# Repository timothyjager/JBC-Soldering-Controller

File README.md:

# JBC-Soldering-Controller

The idea of this project is to make a simple JBC soldering station for the T245. It runs from a 24V DC power supply.
Please note: I burnt out a C210 cartridge using this. I think it would be ok if there was power limiting, so I will try that at some point. 

Tested:

T245 soldering iron

Not tested:

Software - I have kept this because it might be fun to play with at some point, but it is not tested.

AM120 Micro Tweezers (I have not got any yet :( )

Todo:

Automatically changing the GUI depending on if you are using the standard iron or the tweezers.

Possibly change PCB design to make it fit in a box nicely

Design a case for it

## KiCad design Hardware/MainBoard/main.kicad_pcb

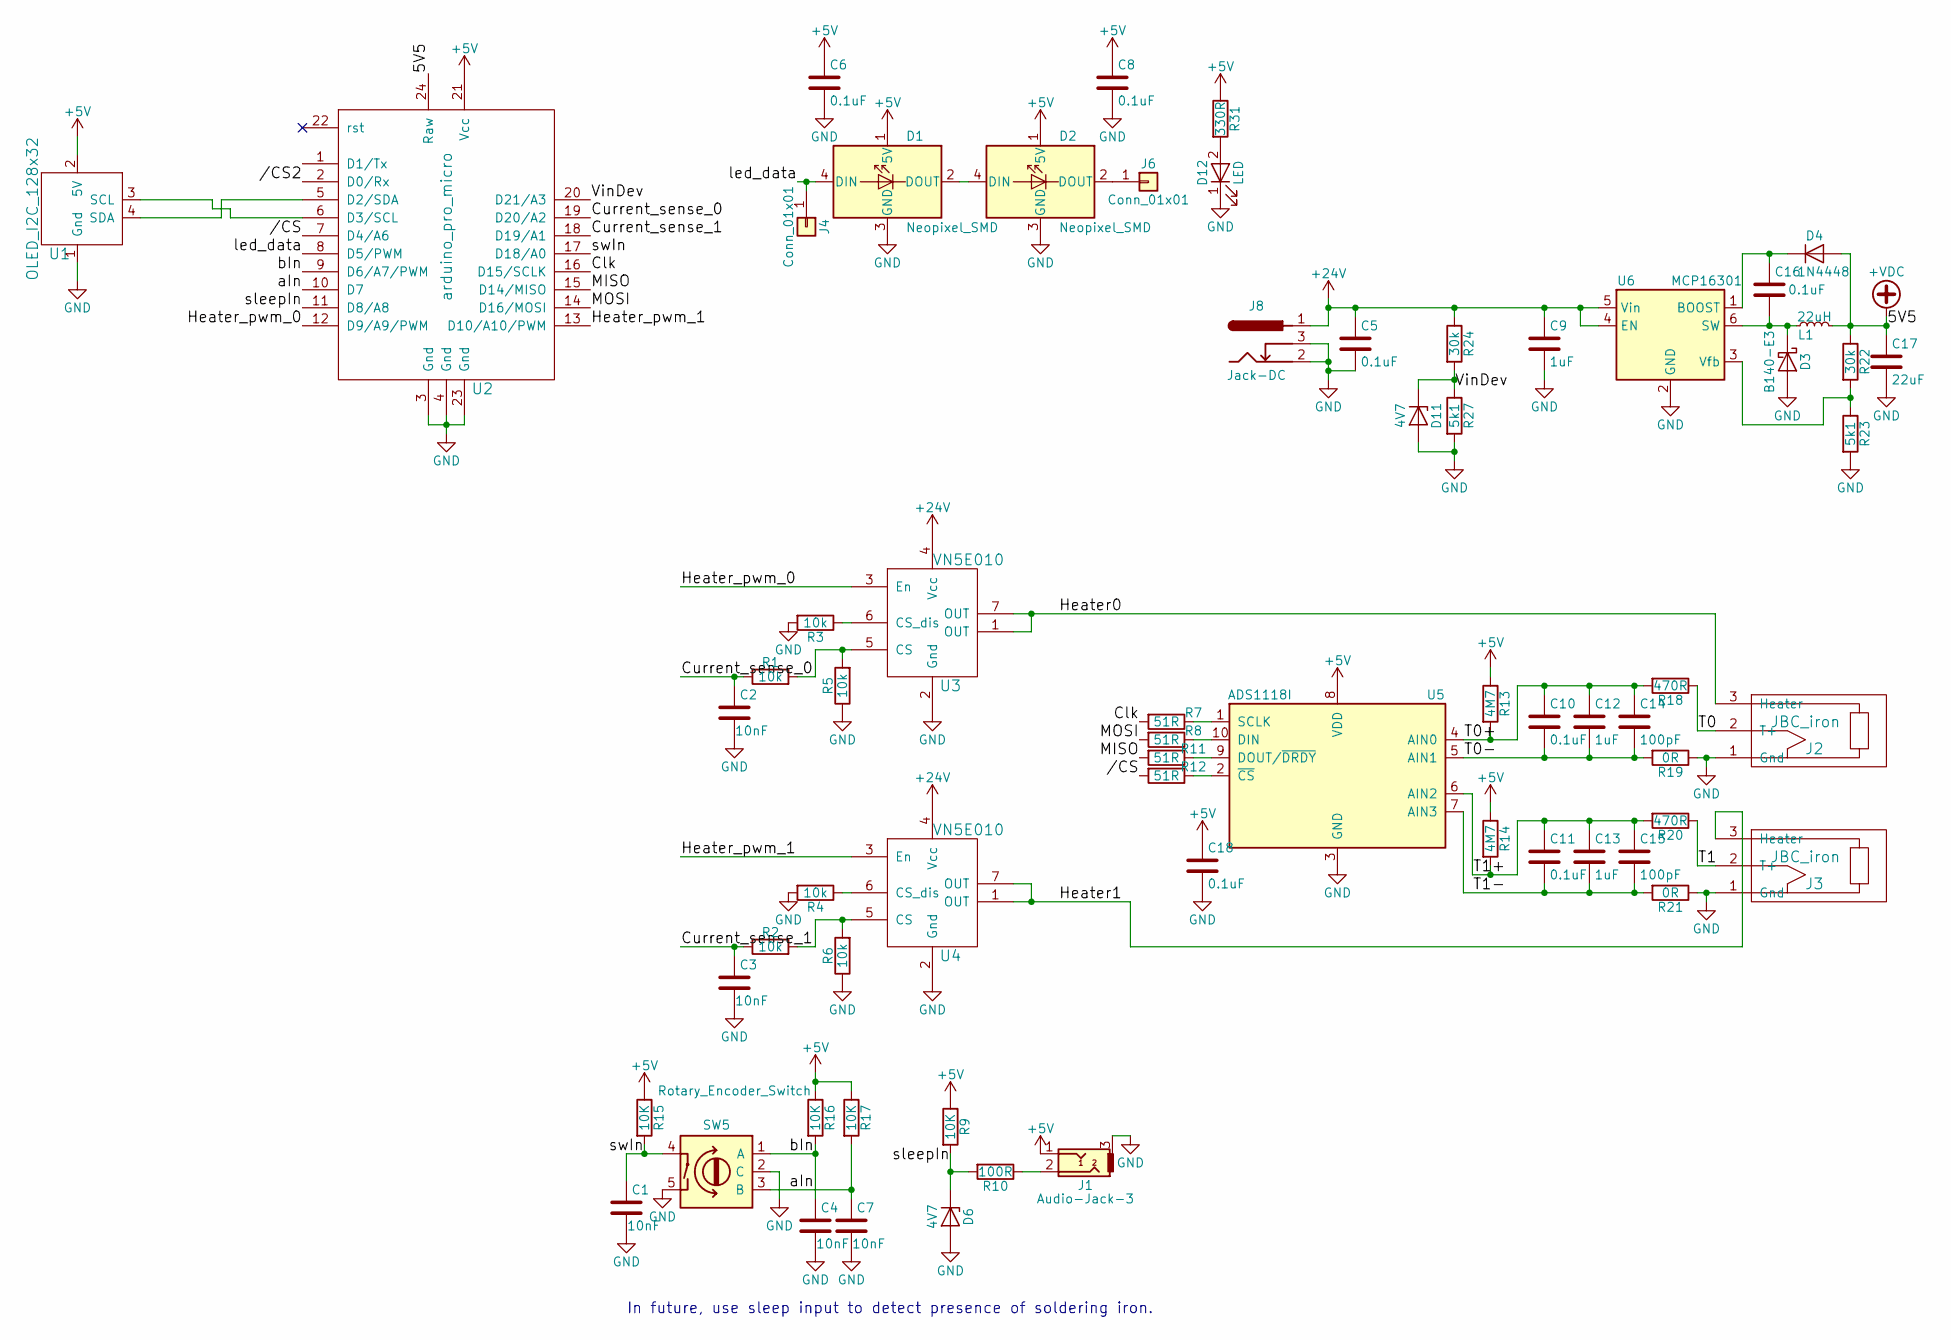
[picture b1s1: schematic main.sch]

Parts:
C1, C2, C3, C4, C7: 10nF; C_0805_HandSoldering
C5, C6, C8, C10, C11, C16, C18: 0.1uF; C_0805_HandSoldering
C9, C12, C13: 1uF; C_0805_HandSoldering
C14, C15: 100pF; C_0805_HandSoldering
C17: 22uF; C_0805_HandSoldering
D1, D2: Neopixel_SMD; 5050-4(L)
D3: B140-E3; D_SMA
D4: 1N4448; D_SOD-123F
D6, D11: 4V7; D_SOD-123F; MPN BZT52-C4V7X
D12: LED; LED_0805_HandSoldering
J1: Audio-Jack-3; 3.5mm_jack; MPN MJ4435-R
J2, J3: JBC_iron; PhoenixContact_MSTBVA-G_03x5.08mm_Vertical
J4, J6: Conn_01x01; Pin_Header_Straight_1x01_Pitch2.54mm
J8: Jack-DC; JACK_ALIM
L1: 22uH; L_6.3x6.3_H3; MPN SRN6045-220M
R1, R2, R3, R4, R5, R6: 10k; R_0805_HandSoldering
R7, R8, R11, R12: 51R; R_0805_HandSoldering
R9, R15, R16, R17: 10K; R_0805_HandSoldering
R10: 100R; R_0805_HandSoldering
R13, R14: 4M7; R_0805_HandSoldering
R18, R20: 470R; R_0805_HandSoldering
R19, R21: 0R; R_0805_HandSoldering
R22, R24: 30k; R_0805_HandSoldering
R23, R27: 5k1; R_0805_HandSoldering
R31: 330R; R_0805_HandSoldering
SW5: Rotary_Encoder_Switch; rot_encoder
U1: OLED_I2C_128x32
U2: arduino_pro_micro; DIP-24_W15.24mm_LongPads
U3, U4: VN5E010; HPAK; MPN VN5E010AHTR-E
U5: ADS1118I; VSSOP_10_HandSoldered; MPN ADS1118IDGST
U6: MCP16301; SOT-23-6; MPN MCP16301T-E/CH

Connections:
+5V: C6.1, C8.1, C18.1, D1.1 (5V), D2.1 (5V), J1.1, R9.1, R13.1, R14.1, R15.1, R16.1, R17.1, R31.1, U1.2 (5V), U2.21 (Vcc), U5.8 (VDD)
+24V: C5.1, C9.1, J8.1, R24.1, U3.4 (Vcc), U4.4 (Vcc), U6.4 (EN), U6.5 (Vin)
+VDC: C17.1, D4.2 (A), L1.2, R22.1, U2.24 (Raw)
//CS: R12.2, U2.7 (D4/A6)
//CS2: U2.2 (D0/Rx)
/Clk: R7.2, U2.16 (D15/SCLK)
/Current_sense_0: C2.1, R1.1, U2.19 (D20/A2)
/Current_sense_1: C3.1, R2.1, U2.18 (D19/A1)
/Heater0: J2.3 (Heater), U3.1 (OUT), U3.7 (OUT)
/Heater1: J3.3 (Heater), U4.1 (OUT), U4.7 (OUT)
/Heater_pwm_0: U2.12 (D9/A9/PWM), U3.3 (En)
/Heater_pwm_1: U2.13 (D10/A10/PWM), U4.3 (En)
/MISO: R11.2, U2.15 (D14/MISO)
/MOSI: R8.2, U2.14 (D16/MOSI)
/T0: J2.2 (T+), R18.1
/T0+: C10.1, C12.1, C14.1, R13.2, R18.2, U5.4 (AIN0)
/T0-: C10.2, C12.2, C14.2, R19.2, U5.5 (AIN1)
/T1: J3.2 (T+), R20.1
/T1+: C11.1, C13.1, C15.1, R14.2, R20.2, U5.6 (AIN2)
/T1-: C11.2, C13.2, C15.2, R21.2, U5.7 (AIN3)
/VinDev: D11.1 (K), R24.2, R27.1, U2.20 (D21/A3)
/aIn: C7.1, R17.2, SW5.3 (B), U2.10 (D7)
/bIn: C4.1, R16.2, SW5.1 (A), U2.9 (D6/A7/PWM)
/led_data: D1.4 (DIN), J4.1, U2.8 (D5/PWM)
/sleepIn: D6.1 (K), R9.2, R10.2, U2.11 (D8/A8)
/swIn: C1.1, R15.2, SW5.4, U2.17 (D18/A0)
GND: C1.2, C2.2, C3.2, C4.2, C5.2, C6.2, C7.2, C8.2, C9.2, C17.2, C18.2, D1.3 (GND), D2.3 (GND), D3.2 (A), D6.2 (A), D11.2 (A), D12.1 (K), J1.3, J2.1 (Gnd), J3.1 (Gnd), J8.2, J8.3, R3.2, R4.2, R5.1, R6.1, R19.1, R21.1, R23.2, R27.2, SW5.2 (C), SW5.5, U1.1 (Gnd), U2.3 (Gnd), U2.4 (Gnd), U2.23 (Gnd), U3.2 (Gnd), U4.2 (Gnd), U5.3 (GND), U6.2 (GND)
unnamed: C16.1, D4.1 (K), U6.1 (BOOST)
unnamed: C16.2, D3.1 (K), L1.1, U6.6 (SW)
unnamed: D1.2 (DOUT), D2.4 (DIN)
unnamed: D2.2 (DOUT), J6.1
unnamed: D12.2 (A), R31.2
unnamed: J1.2, R10.1
unnamed: R1.2, R5.2, U3.5 (CS)
unnamed: R2.2, R6.2, U4.5 (CS)
unnamed: R3.1, U3.6 (CS_dis)
unnamed: R4.1, U4.6 (CS_dis)
unnamed: R7.1, U5.1 (SCLK)
unnamed: R8.1, U5.10 (DIN)
unnamed: R11.1, U5.9 (DOUT/~DRDY)
unnamed: R12.1, U5.2 (~CS)
unnamed: R22.2, R23.1, U6.3 (Vfb)
unnamed: U1.3 (SCL), U2.6 (D3/SCL)
unnamed: U1.4 (SDA), U2.5 (D2/SDA)

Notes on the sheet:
In future, use sleep input to detect presence of soldering iron.

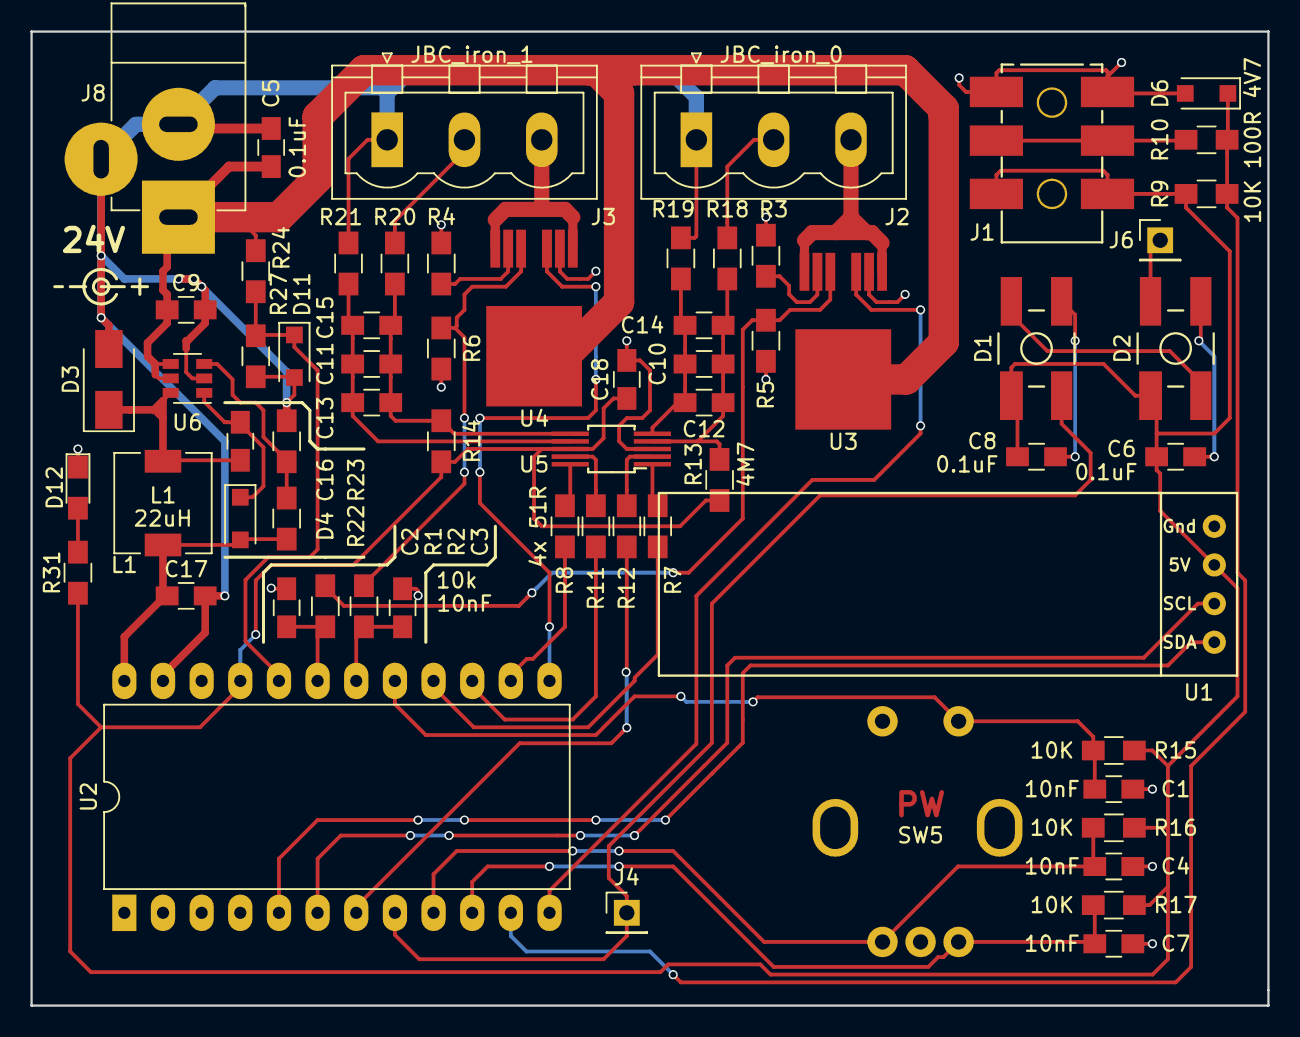
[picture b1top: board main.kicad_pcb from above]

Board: 2 copper layers, 81.3 x 64.0 mm, 65 parts (0 on the bottom side), 43 nets.

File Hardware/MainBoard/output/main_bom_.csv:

Component,Description,Part,References,Value,Footprint,Quantity Per PCB,Datasheet,SPURL,Cost ea @ 100qty,MPN,MFR,SPN,SPR
1,Unpolarized capacitor,C,C5 C6 C8 C10 C11 C16 C18,0.1uF,C_0805_HandSoldering,7,,-,-,-,-,-,-
2,Unpolarized capacitor,C,C14 C15,100pF,C_0805_HandSoldering,2,,-,-,-,-,-,-
3,Unpolarized capacitor,C,C1 C2 C3 C4 C7,10nF,C_0805_HandSoldering,5,,-,-,-,-,-,-
4,Unpolarized capacitor,C,C9 C12 C13,1uF,C_0805_HandSoldering,3,,-,-,-,-,-,-
5,Unpolarized capacitor,C,C17,22uF,C_0805_HandSoldering,1,,-,-,-,-,-,-
6,"100V 0.15A standard switching diode, DO-35",1N4448,D4,1N4448,D_SOD-123F,1,http://www.nxp.com/documents/data_sheet/1N4148_1N4448.pdf,-,-,-,-,-,-
7,Zener Diode,D_Zener,D6 D11,4V7,D_SOD-123F,2,http://www.farnell.com/datasheets/2582331.pdf,http://uk.farnell.com/nexperia/bzt52-c4v7x/zener-diode-aec-q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,0.0258,BZT52-C4V7X,NEXPERIA,2851271,FARNELL
8,"20V 1A Schottky Barrier Rectifier Diode, SMA/DO-214AC",B140-E3,D3,B140-E3,D_SMA,1,http://www.vishay.com/docs/88946/b120.pdf,-,-,-,-,-,-
9,LED generic,LED,D12,LED,LED_0805_HandSoldering,1,,-,-,-,-,-,-
10,"WS2812B (""Neopixel"") digital RGB LED, 5mm/8mm LED package",Neopixel_SMD,D1 D2,Neopixel_SMD,5050-4(L),2,https://www.adafruit.com/product/1938,-,-,-,-,-,-
11,3-pin audio jack receptable (stereo/TRS connector),Audio-Jack-3,J1,Audio-Jack-3,3.5mm_jack,1,MJ4435-R,-,0,-,-,-,-
12,"Generic connector, single row, 01x01",Conn_01x01,J4 J6,Conn_01x01,Pin_Header_Straight_1x01_Pitch2.54mm,2,,-,-,-,-,-,-
13,,JBC_iron,J2 J3,JBC_iron,PhoenixContact_MSTBVA-G_03x5.08mm_Vertical,2,,-,-,-,-,-,-
14,DC Barrel Jack,Jack-DC,J8,Jack-DC,JACK_ALIM,1,,-,-,-,-,-,-
15,"Inductor, small symbol",L_Small,L1,22uH,L_6.3x6.3_H3,1,http://www.farnell.com/datasheets/2366821.pdf,http://uk.farnell.com/bourns/srn6045-220m/inductor-power-22u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,0.423,SRN6045-220M,bourns,2061654,FARNELL
16,Resistor,R,R19 R21,0R,R_0805_HandSoldering,2,,-,-,-,-,-,-
17,Resistor,R,R10,100R,R_0805_HandSoldering,1,,-,-,-,-,-,-
18,Resistor,R,R1 R2 R3 R4 R5 R6 R9 R15 R16 R17,10k,R_0805_HandSoldering,10,,-,-,-,-,-,-
19,Resistor,R,R22 R24,30k,R_0805_HandSoldering,2,,-,-,-,-,-,-
20,Resistor,R,R31,330R,R_0805_HandSoldering,1,,-,0,-,-,-,-
21,Resistor,R,R18 R20,470R,R_0805_HandSoldering,2,,-,-,-,-,-,-
22,Resistor,R,R13 R14,4M7,R_0805_HandSoldering,2,,-,-,-,-,-,-
23,Resistor,R,R7 R8 R11 R12,51R,R_0805_HandSoldering,4,,-,-,-,-,-,-
24,Resistor,R,R23 R27,5k1,R_0805_HandSoldering,2,,-,-,-,-,-,-
25,"Rotary encoder, dual channel, incremental quadrate outputs, with switch",Rotary_Encoder_Switch,SW5,Rotary_Encoder_Switch,rot_encoder,1,,-,-,-,-,-,-
26,"16-bit analog to digital converter, 2 or 4 inputs, integrated temperature sensor, SPI interface",ADS1118I,U5,ADS1118I,VSSOP_10_HandSoldered,1,http://www.ti.com/lit/ds/symlink/ads1118.pdf,http://uk.farnell.com/texas-instruments/ads1118idgst/adc-del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,4.62,ADS1118IDGST,TI,2854467,FARNELL
27,"1A, 4.0 to 30V Input, High Voltage Input integrated switch step-down regulator, SOT-23-6",MCP16301,U6,MCP16301,SOT-23-6,1,http://www.farnell.com/datasheets/2129968.pdf,http://uk.farnell.com/microchip/mcp16301t-e-ch/dc-dc-conv-au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,0.78,MCP16301T-E/CH,microchip,2809949,FARNELL
28,,OLED_I2C_128x32,U1,OLED_I2C_128x32,OLED_I2C_128x32,1,,-,-,-,-,-,-
29,,VN5E010,U3 U4,VN5E010,HPAK,2,http://www.farnell.com/datasheets/2371680.pdf,http://uk.farnell.com/stmicroelectronics/vn5e010ahtr-e/power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,2.32,VN5E010AHTR-E,st,2806822,FARNELL
30,,arduino_pro_micro,U2,arduino_pro_micro,DIP-24_W15.24mm_LongPads,1,,-,-,-,-,-,-
,,,,,,,,,,,,,
,,,,,,,,,,,,,
,,,,,,,,,,,,,
,,,,,,,,,,,,,
,,,,,,,,,,,,,
Component Groups:,30,,,,,,,,,,,,
Component Count:,65,,,,,,,,,,,,
Fitted Components:,65,,,,,,,,,,,,
Number of PCBs:,1,,,,,,,,,,,,
Total components:,65,,,,,,,,,,,,
Schematic Version:,,,,,,,,,,,,,
Schematic Date:,,,,,,,,,,,,,
BoM Date:,16/07/2018 11:32,,,,,,,,,,,,
Schematic Source:,C:/Users/paul.withers/Google Drive/Soldering Iron/myProject2/main.sch,,,,,,,,,,,,
KiCad Version:,Eeschema 4.0.7,,,,,,,,,,,,

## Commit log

2017-05-14 updated header
2017-05-14 updated comments per data sheet
2017-05-14 added OLED support and Dell adapter module
2017-05-15 added HW/FW folders
2017-05-16 moved to new folder per arduino requirements
2017-05-16 added header file github links
2017-05-16 moved ADS1118 internal temp function to header file
2017-05-16 pin mapping
2017-05-17 added EEPROM and EEWrap libraries for NVOL data
2017-05-23 added initial PID controller
2017-05-23 stubbing out PID and calibration
2017-05-23 ads1118 ADC datasheet
2017-05-23 added call to pid.compute
2017-05-24 checkin after testing high side driver. Driver works, but messes up ADC reading.. need to debug.
2017-05-24 #define wasn't calculating correctly so i hard coded it for testing. now ADC reading works while the heater is on.
2017-06-01 integrated serial comm to PC. Initial PID testing success. lots of test code. needs cleanup, and some refactoring.
2017-06-09 integrated encoder, tested PSU detect, misc temp code for testing.
2017-06-09 added datasheet for high side driver
2017-06-11 Initial Schematic Commit
2017-06-11 deleted step file
2017-06-11 added OLED
2017-06-12 schematic progress check-in.
2017-06-13 replaced DC DC converter.
2017-06-14 misc schematic cleanup & consolidation
2017-06-16 added model for DELL power jack
2017-06-21 created dell power adapter footprint. though i may end up using a differnt part due to clearance issues.
2017-06-23 added model for alternate dell power connector
2017-06-24 added controller assembly
2017-06-25 Preliminary case concept
2017-06-25 added power plug and USB plug to ensure proper fit
2017-06-26 added standoffs and 2.5mm jack
2017-06-26 misc component updates
2017-06-29 added cradle detect
2017-06-29 added 2.5mm phono jack
2017-06-29 misc model updates
2017-06-29 step files
2017-06-30 misc updates to PCB and components
2017-07-02 added screws, misc schematic improvements, removed warnings
2017-07-03 ROUTING IN PROGRESS
2017-07-07 moved 3.5mm jack pos. fixed all PCB DRC errors
2017-07-10 misc routing cleanup
2017-07-13 Misc project organization updates. Adding project params and sheet params
2017-07-17 v1.0 Release as submitted to PCB vendor
2017-07-17 misc updates: rounded board corners, centering encoder, etc.
2017-07-17 workspace commit
2017-08-12 updated BOM
2018-01-20 Remapped IO to match final PCB. Tested peripherals. Heater, LED, Temperature, ADC, Voltage Sense, Cradle, etc.
2018-01-20 Misc. Schematic cleanup
2018-01-20 initial commit. Needs refinement.
2018-01-20 Misc. Changes to support PID tuning application
2018-01-20 UI cleanup. Added simulated input option.
2018-01-21 refactoring and organizing code. in progress.
2018-01-21 refactoring. commenting.
2018-01-22 Refactored communication between arduino and labVIEW
2018-01-22 refactored data structures and comm. strategy.
2018-01-23 PID tuning. Some quick implementations of key functions to prepare for demo. Lots of refactoring is needed.
2018-01-23 fixed bug in display refresh logic.
2018-01-26 added schematic
2018-01-30 misc debugging. error investigation.
2018-01-30 changed PWM display limits
2018-01-30 saved project settings.
2018-08-04 Update to get rid of reset pin for oled
    Update to globals.ino so that an oled_reset pin is not needed when using the Adafruit_SSD1206 library.
2018-11-01 Added tweezer functionality
    This includes a new PCB layout, done in KiCad. This is so it is possible to use tweezers.
    The firmware has been changed to acomidate this. The interrupt part has changed a lot to allow both outputs to be individually controlled at the same time.
2018-11-01 updated readme
    Updated readme to make it clearer
2018-11-20 change of file name
2019-02-12 added option to disable simulaneous outputs.
    Added an option to disable both outputs turning on at the same time.
    Set disable_simultaneous_output to true to enable.
